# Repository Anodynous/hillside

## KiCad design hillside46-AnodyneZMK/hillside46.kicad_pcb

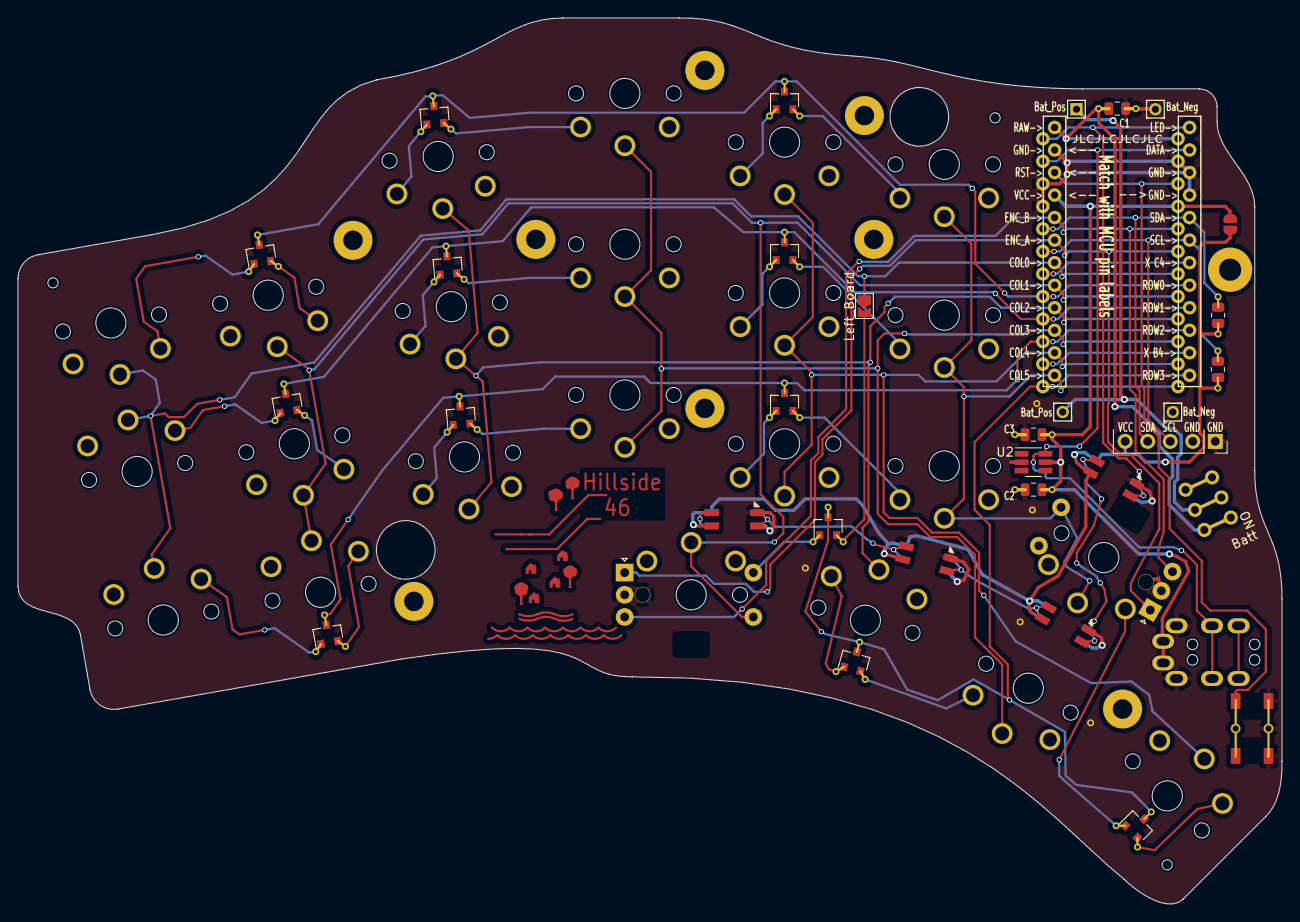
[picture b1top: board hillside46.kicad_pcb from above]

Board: 2 copper layers, 142.5 x 99.9 mm, 86 parts (0 on the bottom side), 49 nets.

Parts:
C1, C2, C3: 4u7; C_0805_2012Metric
D1, D2, D3, D4: SK6812-MINI-E
D7, D8, D9, D10, D11, D12, D13, D14, D15, D19, D20, D21: BAV70; SOT-23
H1: Mount_Tenting; Tenting_Puck
H2, H8, H9, H10, H11, H12, H13, H14, H15, H16, H17, H18, H19, H20, H21, H22: Bumpon
H3: Logo; Hillside_Logo
H4, H5, H6, H7: MountHole; MountingHole_2.2mm_with_PCB_insert_rings
H23, H24, H25: ToolingHole; ToolingHole_1.152mm
J1: Haptic; Pimoroni_Haptic
J2: TRRS; MJ-4PP-9
J3, J5: Bat_Pos; 1pin_conn
J4, J6: Bat_Neg; 1pin_conn
JP1: VccJumper; SolderJumper-2_P1.3mm_Bridged_RoundedPad1.0x1.5mm
JP2: Left_Board; SolderJumper-2_P1.3mm_Open_TrianglePad1.0x1.5mm
K1, K2, K3, K4, K5, K6, K7, K8, K9, K10, K11, K12, K13, K14, K15, K16, K17, K18, K21, K22, K23: SW_Key; pg1350-R_hotswap
K19, K20: SW_Rotary; pg1350-DR_rotary_hotswap
R1, R2: 4.7k; R_0805_2012Metric
SW1: SKQGAFE010; SW_SPST_SKQG_WithStem
SW2: SW_Power; SW_SPDT_JS202011AQN
U1: ProMicro_r; ProMicro_v2
U2: SRV05-4; SOT-23-6_Handsoldering_threenumbered
V1, V2, V3, V4, V5: Via; VIA-0.8mm

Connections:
GND: C1.2, C2.1, C3.1, D1.3 (VSS), D2.3 (VSS), D3.3 (VSS), D4.3 (VSS), J1.1, J1.2, J2.T (Tip), J4.1, J6.1, K19.C, K20.C, SW1.2, U1.3 (GND), U1.4 (GND), U1.23 (GND), U2.2 (VN), V1.1 (via), V2.1 (via), V3.1 (via), V4.1 (via), V5.1 (via)
LED: D1.4 (DIN), U1.1 (D3/TX0)
unnamed: D1.2 (DOUT), D2.4 (DIN)
unnamed: D2.2 (DOUT), D3.4 (DIN)
unnamed: D3.2 (DOUT), D4.4 (DIN)
unnamed: D7.1 (A1), K1.2
unnamed: D7.2 (A2), K2.2
unnamed: D8.1 (A1), K3.2
unnamed: D8.2 (A2), K4.2
unnamed: D9.1 (A1), K5.2
unnamed: D9.2 (A2), K6.2
unnamed: D10.1 (A1), K7.2
unnamed: D10.2 (A2), K8.2
unnamed: D11.1 (A1), K9.2
unnamed: D11.2 (A2), K10.2
unnamed: D12.1 (A1), K11.2
unnamed: D12.2 (A2), K12.2
unnamed: D13.1 (A1), K13.2
unnamed: D13.2 (A2), K14.2
unnamed: D14.1 (A1), K15.2
unnamed: D14.2 (A2), K16.2
unnamed: D15.1 (A1), K17.2
unnamed: D15.2 (A2), K18.2
unnamed: D19.1 (A1), K20.S2
unnamed: D19.2 (A2), JP2.2 (B)
unnamed: D20.1 (A1), K21.2
unnamed: D20.2 (A2), K22.2
unnamed: D21.1 (A1), K19.S2
unnamed: D21.2 (A2), K23.2
SCL: J1.3, R1.2, U1.6 (SCL/D0/3)
SDA: J1.4, R2.2, U1.5 (SDA/D1/2)
VCC: C2.2, C3.2, J2.S (Sleeve), JP1.1 (A), U1.21 (VCC), U2.5 (VP)
VCC_ACC: D1.1 (VDD), D2.1 (VDD), D3.1 (VDD), D4.1 (VDD), J1.5, JP1.2 (B), R1.1, R2.1
bat+: J3.1, J5.1, SW2.2 (B)
col0: JP2.1 (A), K1.1, K7.1, K13.1, U1.18 (A1/F6)
col1: K2.1, K8.1, K14.1, K20.S1, U1.17 (A0/F7)
col2: K3.1, K9.1, K15.1, K21.1, U1.16 (15/B1)
col3: K4.1, K10.1, K16.1, K22.1, U1.15 (14/B3)
col4: K5.1, K11.1, K17.1, K23.1, U1.14 (16/B2)
col5: K6.1, K12.1, K18.1, K19.S1, U1.13 (10/B6)
data: J2.R1 (Ring1), U1.2 (D2/RX1), U2.6 (IO4)
enc_a: K19.A, K20.A, U1.19 (A2/F5)
enc_b: K19.B, K20.B, U1.20 (A3/F4)
raw: C1.1, SW2.3 (C), U1.24 (RAW)
reset: SW1.1, U1.22 (RST)
row0: D7.3 (K), D8.3 (K), D9.3 (K), U1.8 (C6/5)
row1: D10.3 (K), D11.3 (K), D12.3 (K), U1.9 (D7/6)
row2: D13.3 (K), D14.3 (K), D15.3 (K), U1.10 (E6/7)
row3: D19.3 (K), D20.3 (K), D21.3 (K), U1.12 (B5/9)

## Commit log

2026-02-02 create hillside46-AnodyneZMK
2026-02-02 upgrade kicad file version
2026-02-02 remove pinkie column cutouts
2026-02-02 clean up silkscreen
2026-02-02 cut VccJumper trace for wireless
2026-02-02 remove puck silkscreen circle
2026-02-02 remove LED cut-outs
2026-02-02 refill zones and perform DRC
2026-02-02 exclude invalid DRC errors, generate gerber files
2026-02-20 add ZMK builds directory to gitignore
2026-02-20 add DRC exclusions
